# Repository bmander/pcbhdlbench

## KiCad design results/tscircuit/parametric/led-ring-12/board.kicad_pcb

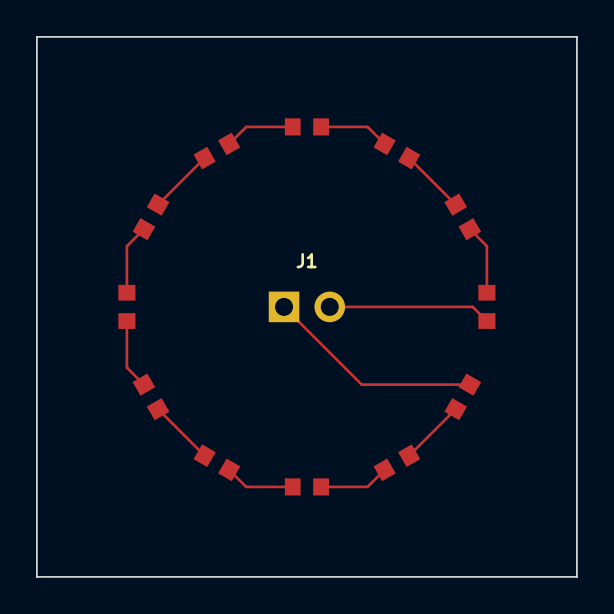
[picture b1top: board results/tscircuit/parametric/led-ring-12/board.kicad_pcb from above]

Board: 2 copper layers, 30.0 x 30.0 mm, 13 parts (0 on the bottom side), 13 nets.

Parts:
D1, D2, D3, D4, D5, D6, D7, D8, D9, D10, D11, D12: LED; led
J1: J1; pin_header_pinrow2_p2_54_id1_od1_7_nopinlabels

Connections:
.D1 > .anode to .D2 > .cathode: D1.1, D2.2
.D2 > .anode to .D3 > .cathode: D2.1, D3.2
.D3 > .anode to .D4 > .cathode: D3.1, D4.2
.D4 > .anode to .D5 > .cathode: D4.1, D5.2
.D5 > .anode to .D6 > .cathode: D5.1, D6.2
.D6 > .anode to .D7 > .cathode: D6.1, D7.2
.D7 > .anode to .D8 > .cathode: D7.1, D8.2
.D8 > .anode to .D9 > .cathode: D8.1, D9.2
.D9 > .anode to .D10 > .cathode: D9.1, D10.2
.D10 > .anode to .D11 > .cathode: D10.1, D11.2
.D11 > .anode to .D12 > .cathode: D11.1, D12.2
.J1 > .pin1 to .D12 > .anode: D12.1, J1.1
.J1 > .pin2 to .D1 > .cathode: D1.2, J1.2

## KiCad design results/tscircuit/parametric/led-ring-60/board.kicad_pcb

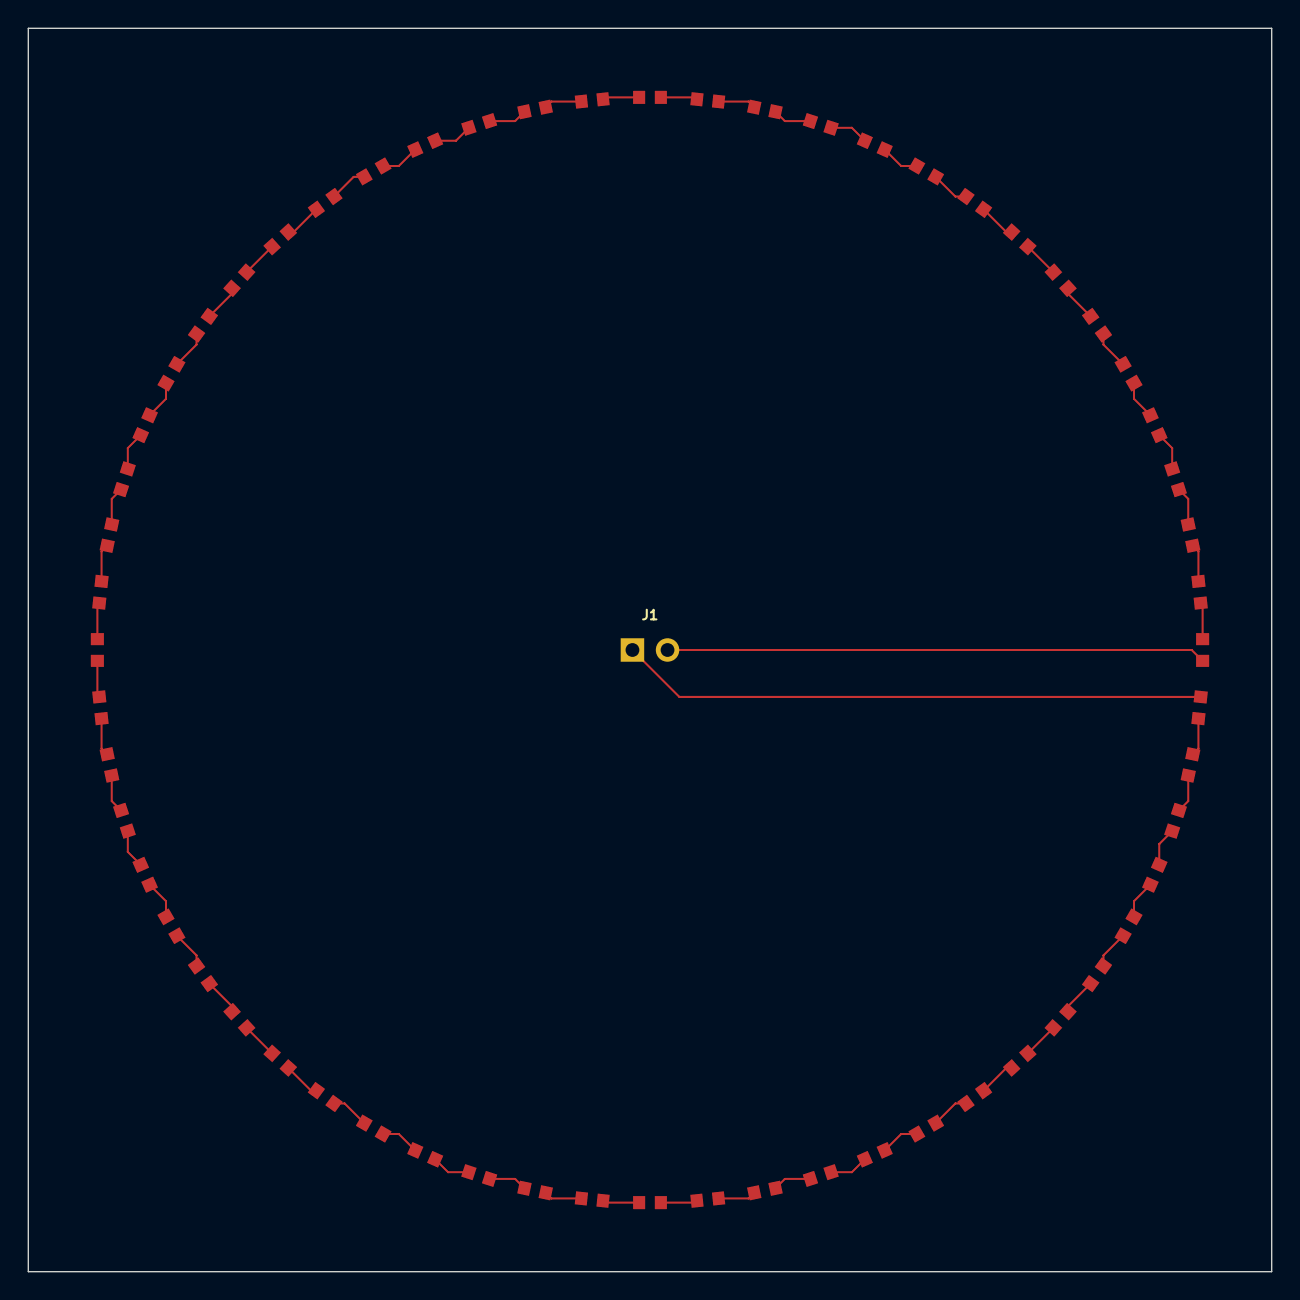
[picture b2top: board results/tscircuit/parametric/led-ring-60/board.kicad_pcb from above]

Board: 2 copper layers, 90.0 x 90.0 mm, 61 parts (0 on the bottom side), 61 nets.

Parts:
D1, D2, D3, D4, D5, D6, D7, D8, D9, D10, D11, D12, D13, D14, D15, D16, D17, D18, D19, D20, D21, D22, D23, D24, D25, D26, D27, D28, D29, D30, D31, D32, D33, D34, D35, D36, D37, D38, D39, D40, D41, D42, D43, D44, D45, D46, D47, D48, D49, D50, D51, D52, D53, D54, D55, D56, D57, D58, D59, D60: LED; led
J1: J1; pin_header_pinrow2_p2_54_id1_od1_7_nopinlabels

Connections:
.D1 > .anode to .D2 > .cathode: D1.1, D2.2
.D2 > .anode to .D3 > .cathode: D2.1, D3.2
.D3 > .anode to .D4 > .cathode: D3.1, D4.2
.D4 > .anode to .D5 > .cathode: D4.1, D5.2
.D5 > .anode to .D6 > .cathode: D5.1, D6.2
.D6 > .anode to .D7 > .cathode: D6.1, D7.2
.D7 > .anode to .D8 > .cathode: D7.1, D8.2
.D8 > .anode to .D9 > .cathode: D8.1, D9.2
.D9 > .anode to .D10 > .cathode: D9.1, D10.2
.D10 > .anode to .D11 > .cathode: D10.1, D11.2
.D11 > .anode to .D12 > .cathode: D11.1, D12.2
.D12 > .anode to .D13 > .cathode: D12.1, D13.2
.D13 > .anode to .D14 > .cathode: D13.1, D14.2
.D14 > .anode to .D15 > .cathode: D14.1, D15.2
.D15 > .anode to .D16 > .cathode: D15.1, D16.2
.D16 > .anode to .D17 > .cathode: D16.1, D17.2
.D17 > .anode to .D18 > .cathode: D17.1, D18.2
.D18 > .anode to .D19 > .cathode: D18.1, D19.2
.D19 > .anode to .D20 > .cathode: D19.1, D20.2
.D20 > .anode to .D21 > .cathode: D20.1, D21.2
.D21 > .anode to .D22 > .cathode: D21.1, D22.2
.D22 > .anode to .D23 > .cathode: D22.1, D23.2
.D23 > .anode to .D24 > .cathode: D23.1, D24.2
.D24 > .anode to .D25 > .cathode: D24.1, D25.2
.D25 > .anode to .D26 > .cathode: D25.1, D26.2
.D26 > .anode to .D27 > .cathode: D26.1, D27.2
.D27 > .anode to .D28 > .cathode: D27.1, D28.2
.D28 > .anode to .D29 > .cathode: D28.1, D29.2
.D29 > .anode to .D30 > .cathode: D29.1, D30.2
.D30 > .anode to .D31 > .cathode: D30.1, D31.2
.D31 > .anode to .D32 > .cathode: D31.1, D32.2
.D32 > .anode to .D33 > .cathode: D32.1, D33.2
.D33 > .anode to .D34 > .cathode: D33.1, D34.2
.D34 > .anode to .D35 > .cathode: D34.1, D35.2
.D35 > .anode to .D36 > .cathode: D35.1, D36.2
.D36 > .anode to .D37 > .cathode: D36.1, D37.2
.D37 > .anode to .D38 > .cathode: D37.1, D38.2
.D38 > .anode to .D39 > .cathode: D38.1, D39.2
.D39 > .anode to .D40 > .cathode: D39.1, D40.2
.D40 > .anode to .D41 > .cathode: D40.1, D41.2
.D41 > .anode to .D42 > .cathode: D41.1, D42.2
.D42 > .anode to .D43 > .cathode: D42.1, D43.2
.D43 > .anode to .D44 > .cathode: D43.1, D44.2
.D44 > .anode to .D45 > .cathode: D44.1, D45.2
.D45 > .anode to .D46 > .cathode: D45.1, D46.2
.D46 > .anode to .D47 > .cathode: D46.1, D47.2
.D47 > .anode to .D48 > .cathode: D47.1, D48.2
.D48 > .anode to .D49 > .cathode: D48.1, D49.2
.D49 > .anode to .D50 > .cathode: D49.1, D50.2
.D50 > .anode to .D51 > .cathode: D50.1, D51.2
.D51 > .anode to .D52 > .cathode: D51.1, D52.2
.D52 > .anode to .D53 > .cathode: D52.1, D53.2
.D53 > .anode to .D54 > .cathode: D53.1, D54.2
.D54 > .anode to .D55 > .cathode: D54.1, D55.2
.D55 > .anode to .D56 > .cathode: D55.1, D56.2
.D56 > .anode to .D57 > .cathode: D56.1, D57.2
.D57 > .anode to .D58 > .cathode: D57.1, D58.2
.D58 > .anode to .D59 > .cathode: D58.1, D59.2
.D59 > .anode to .D60 > .cathode: D59.1, D60.2
.J1 > .pin1 to .D60 > .anode: D60.1, J1.1
.J1 > .pin2 to .D1 > .cathode: D1.2, J1.2

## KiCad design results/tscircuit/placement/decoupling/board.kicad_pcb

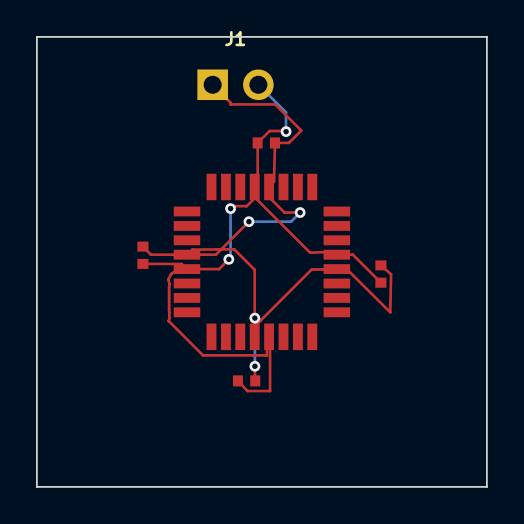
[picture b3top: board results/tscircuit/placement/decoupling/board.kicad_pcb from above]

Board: 2 copper layers, 25.0 x 25.0 mm, 6 parts (0 on the bottom side), 2 nets.

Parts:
C1, C2, C3, C4: 100nF; capacitor
J1: J1; pin_header_pinrow2_p2_54_id1_od1_7_nopinlabels
U1: chip

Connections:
GND: C1.2, C2.2, C3.2, C4.2, J1.2, U1.5, U1.13, U1.21, U1.29
VDD: C1.1, C2.1, C3.1, C4.1, J1.1, U1.4, U1.12, U1.20, U1.28

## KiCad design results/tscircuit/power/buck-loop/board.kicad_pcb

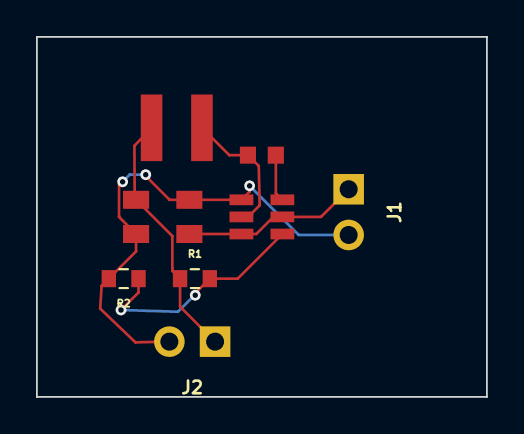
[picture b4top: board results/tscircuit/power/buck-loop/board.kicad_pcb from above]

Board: 2 copper layers, 25.0 x 20.0 mm, 9 parts (0 on the bottom side), 6 nets.

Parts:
C1: 10uF; capacitor
C2: 100nF; capacitor
C3: 22uF; capacitor
J1: J1; pin_header_pinrow2_p2_54_id1_od1_7_nopinlabels
J2: J2; pin_header_pinrow2_p2_54_id1_od1_7_nopinlabels
L1: 2.2µH; inductor
R1: 33kΩ; resistor_res0603
R2: 10kΩ; resistor_res0603
U1: chip

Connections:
BST: C2.1, U1.6
FB: R1.2, R2.1, U1.4
GND: C1.2, C3.2, J1.2, J2.2, R2.2, U1.1
SW: C2.2, L1.1, U1.2
VIN: C1.1, J1.1, U1.3, U1.5
VOUT: C3.1, J2.1, L1.2, R1.1

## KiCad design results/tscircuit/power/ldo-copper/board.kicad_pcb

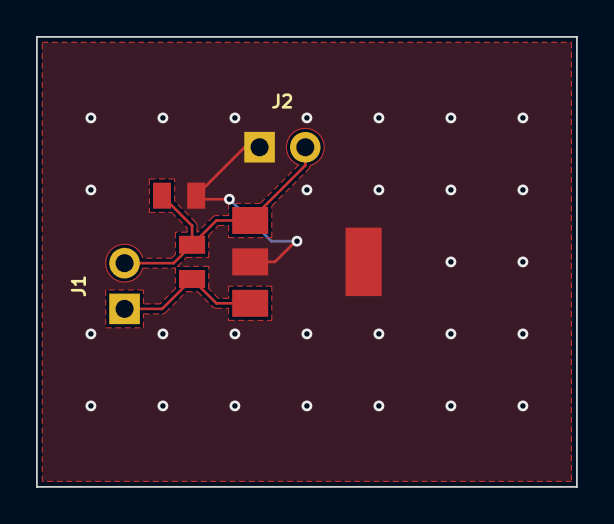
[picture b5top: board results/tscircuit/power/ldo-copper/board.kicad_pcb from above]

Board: 2 copper layers, 30.0 x 25.0 mm, 5 parts (0 on the bottom side), 3 nets.

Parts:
C1: 10uF; capacitor
C2: 22uF; capacitor
J1: J1; pin_header_pinrow2_p2_54_id1_od1_7_nopinlabels
J2: J2; pin_header_pinrow2_p2_54_id1_od1_7_nopinlabels
U1: chip

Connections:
GND: C1.2, C2.2, J1.2, J2.2, U1.1
VIN: C1.1, J1.1, U1.3
VOUT: C2.1, J2.1, U1.2

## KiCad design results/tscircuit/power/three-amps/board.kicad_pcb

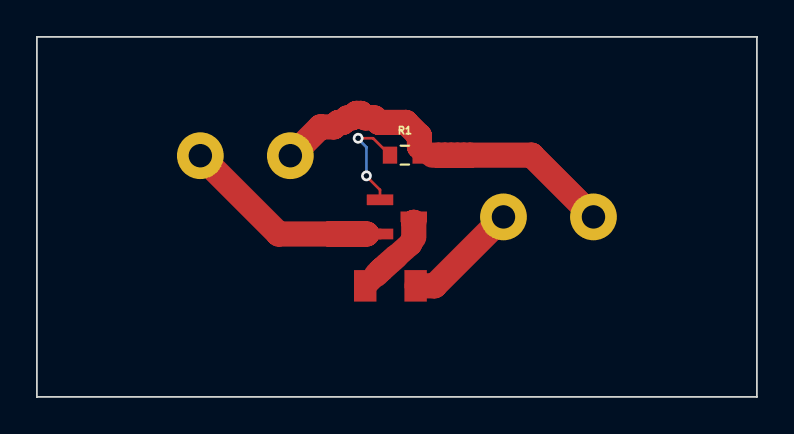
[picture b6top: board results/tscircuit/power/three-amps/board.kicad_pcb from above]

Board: 2 copper layers, 40.0 x 20.0 mm, 5 parts (0 on the bottom side), 5 nets.

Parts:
F1: chip
J1, J2: chip
Q1: chip
R1: 100kΩ; resistor_res0603

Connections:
.F1 > .pin2 to .Q1 > .D: F1.2, Q1.3
.J1 > .pin1 to .F1 > .pin1: F1.1, J1.1
.J2 > .pin2 to .J1 > .pin2: J1.2, J2.2, R1.2
.Q1 > .G to .R1 > .pin1: Q1.1, R1.1
.Q1 > .S to .J2 > .pin1: J2.1, Q1.2

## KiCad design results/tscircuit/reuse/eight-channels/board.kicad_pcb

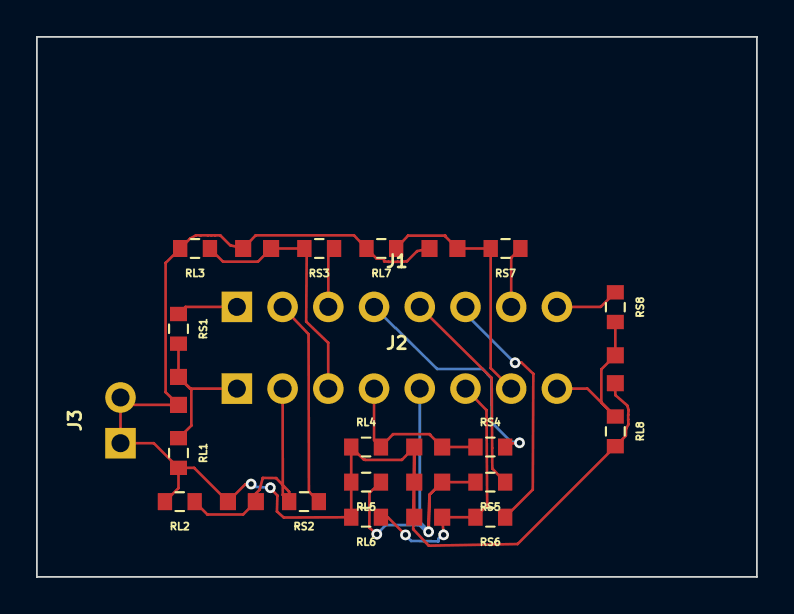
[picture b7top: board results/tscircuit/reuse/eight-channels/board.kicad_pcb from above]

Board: 2 copper layers, 40.0 x 30.0 mm, 27 parts (0 on the bottom side), 17 nets.

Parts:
C1, C2, C3, C4, C5, C6, C7, C8: 100nF; capacitor
J1: J1; pin_header_pinrow8_p2_54_id1_od1_7_nopinlabels
J2: J2; pin_header_pinrow8_p2_54_id1_od1_7_nopinlabels
J3: J3; pin_header_pinrow2_p2_54_id1_od1_7_nopinlabels
RL1, RL2, RL3, RL4, RL5, RL6, RL7, RL8: 100kΩ; resistor_res0603
RS1, RS2, RS3, RS4, RS5, RS6, RS7, RS8: 1kΩ; resistor_res0603

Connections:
GND: C1.2, C2.2, C3.2, C4.2, C5.2, C6.2, C7.2, C8.2, J3.1, J3.2, RL1.2, RL2.2, RL3.2, RL4.2, RL5.2, RL6.2, RL7.2, RL8.2
IN1: J1.1, RS1.1
IN2: J1.2, RS2.1
IN3: J1.3, RS3.1
IN4: J1.4, RS4.1
IN5: J1.5, RS5.1
IN6: J1.6, RS6.1
IN7: J1.7, RS7.1
IN8: J1.8, RS8.1
OUT1: C1.1, J2.1, RL1.1, RS1.2
OUT2: C2.1, J2.2, RL2.1, RS2.2
OUT3: C3.1, J2.3, RL3.1, RS3.2
OUT4: C4.1, J2.4, RL4.1, RS4.2
OUT5: C5.1, J2.5, RL5.1, RS5.2
OUT6: C6.1, J2.6, RL6.1, RS6.2
OUT7: C7.1, J2.7, RL7.1, RS7.2
OUT8: C8.1, J2.8, RL8.1, RS8.2

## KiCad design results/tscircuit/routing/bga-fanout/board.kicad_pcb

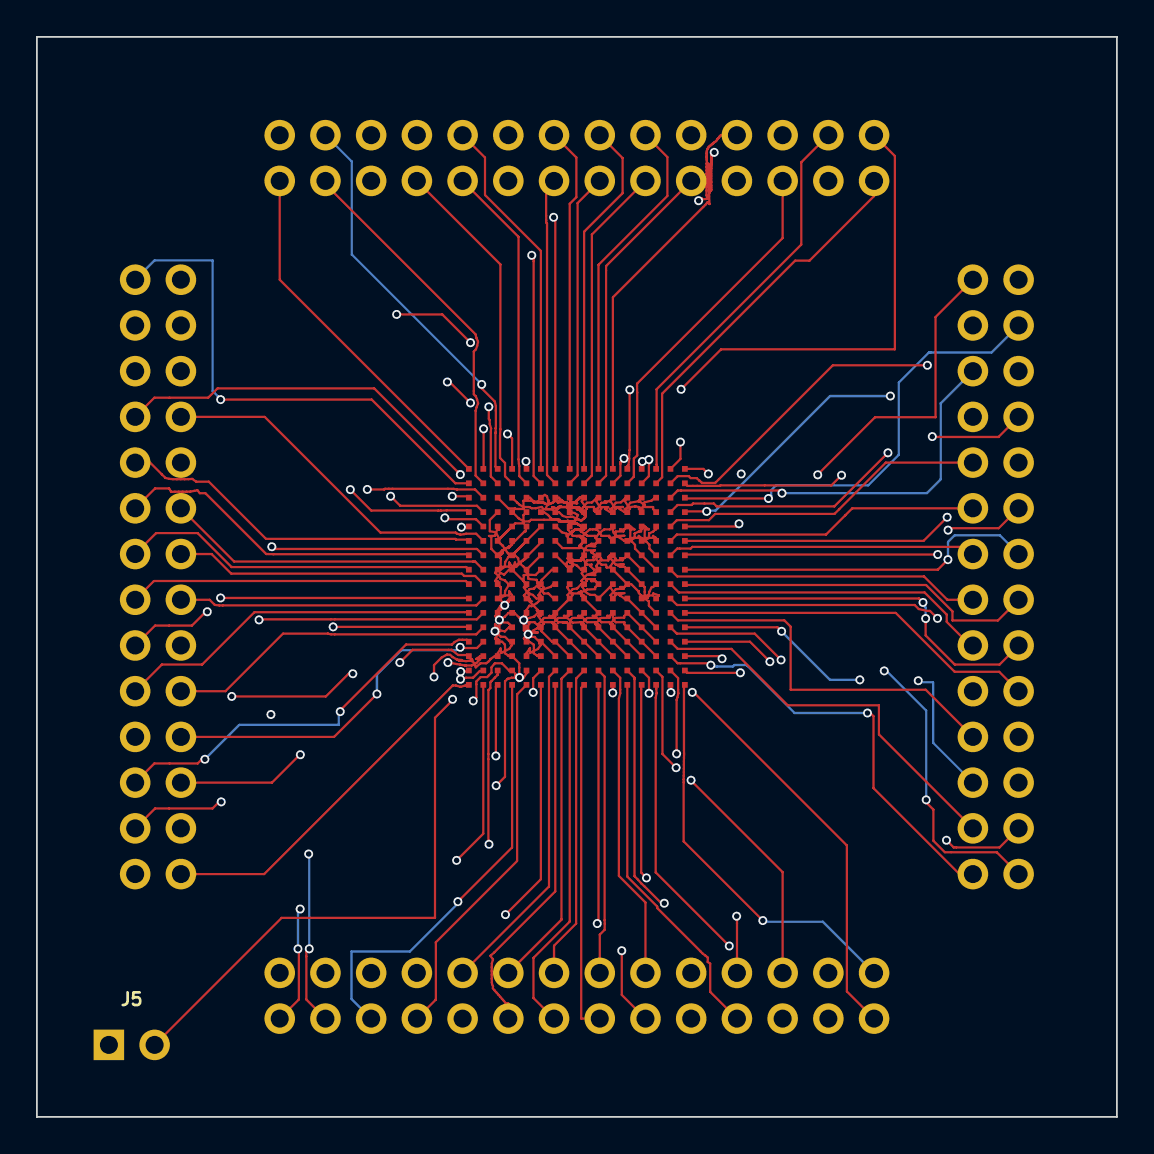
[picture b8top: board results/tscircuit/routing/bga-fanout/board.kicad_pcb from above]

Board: 4 copper layers, 60.0 x 60.0 mm, 6 parts (0 on the bottom side), 114 nets.

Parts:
J1, J2, J3, J4: chip
J5: J5; pin_header_pinrow2_p2_54_id1_od1_7_nopinlabels
U1: chip

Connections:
.U1 > .A1 to .J1 > .pin1: J1.1, U1.1
.U1 > .A2 to .J1 > .pin2: J1.2, U1.2
.U1 > .A3 to .J1 > .pin4: J1.4, U1.3
.U1 > .A4 to .J1 > .pin6: J1.6, U1.4
.U1 > .A5 to .J1 > .pin8: J1.8, U1.5
.U1 > .A6 to .J1 > .pin10: J1.10, U1.6
.U1 > .A7 to .J1 > .pin12: J1.12, U1.7
.U1 > .A8 to .J1 > .pin14: J1.14, U1.8
.U1 > .A9 to .J1 > .pin16: J1.16, U1.9
.U1 > .A10 to .J1 > .pin18: J1.18, U1.10
.U1 > .A11 to .J1 > .pin20: J1.20, U1.11
.U1 > .A12 to .J1 > .pin22: J1.22, U1.12
.U1 > .A13 to .J1 > .pin24: J1.24, U1.13
.U1 > .A14 to .J1 > .pin26: J1.26, U1.14
.U1 > .A15 to .J1 > .pin28: J1.28, U1.15
.U1 > .A16 to .J2 > .pin1: J2.1, U1.16
.U1 > .B1 to .J4 > .pin28: J4.28, U1.17
.U1 > .B2 to .J1 > .pin3: J1.3, U1.18
.U1 > .B3 to .J1 > .pin5: J1.5, U1.19
.U1 > .B4 to .J1 > .pin7: J1.7, U1.20
.U1 > .B5 to .J1 > .pin9: J1.9, U1.21
.U1 > .B6 to .J1 > .pin11: J1.11, U1.22
.U1 > .B7 to .J1 > .pin13: J1.13, U1.23
.U1 > .B8 to .J1 > .pin15: J1.15, U1.24
.U1 > .B9 to .J1 > .pin17: J1.17, U1.25
.U1 > .B10 to .J1 > .pin19: J1.19, U1.26
.U1 > .B11 to .J1 > .pin21: J1.21, U1.27
.U1 > .B12 to .J1 > .pin23: J1.23, U1.28
.U1 > .B13 to .J1 > .pin25: J1.25, U1.29
.U1 > .B14 to .J1 > .pin27: J1.27, U1.30
.U1 > .B15 to .J2 > .pin3: J2.3, U1.31
.U1 > .B16 to .J2 > .pin2: J2.2, U1.32
.U1 > .C1 to .J4 > .pin26: J4.26, U1.33
.U1 > .C2 to .J4 > .pin27: J4.27, U1.34
.U1 > .C15 to .J2 > .pin5: J2.5, U1.47
.U1 > .C16 to .J2 > .pin4: J2.4, U1.48
.U1 > .D1 to .J4 > .pin24: J4.24, U1.49
.U1 > .D2 to .J4 > .pin25: J4.25, U1.50
.U1 > .D15 to .J2 > .pin7: J2.7, U1.63
.U1 > .D16 to .J2 > .pin6: J2.6, U1.64
.U1 > .E1 to .J4 > .pin22: J4.22, U1.65
.U1 > .E2 to .J4 > .pin23: J4.23, U1.66
.U1 > .E15 to .J2 > .pin9: J2.9, U1.79
.U1 > .E16 to .J2 > .pin8: J2.8, U1.80
.U1 > .F1 to .J4 > .pin20: J4.20, U1.81
.U1 > .F2 to .J4 > .pin21: J4.21, U1.82
.U1 > .F15 to .J2 > .pin11: J2.11, U1.95
.U1 > .F16 to .J2 > .pin10: J2.10, U1.96
.U1 > .G1 to .J4 > .pin18: J4.18, U1.97
.U1 > .G2 to .J4 > .pin19: J4.19, U1.98
.U1 > .G15 to .J2 > .pin13: J2.13, U1.111
.U1 > .G16 to .J2 > .pin12: J2.12, U1.112
.U1 > .H1 to .J4 > .pin16: J4.16, U1.113
.U1 > .H2 to .J4 > .pin17: J4.17, U1.114
.U1 > .H15 to .J2 > .pin15: J2.15, U1.127
.U1 > .H16 to .J2 > .pin14: J2.14, U1.128
.U1 > .J1 to .J4 > .pin14: J4.14, U1.129
.U1 > .J2 to .J4 > .pin15: J4.15, U1.130
.U1 > .J15 to .J2 > .pin17: J2.17, U1.143
.U1 > .J16 to .J2 > .pin16: J2.16, U1.144
.U1 > .K1 to .J4 > .pin12: J4.12, U1.145
.U1 > .K2 to .J4 > .pin13: J4.13, U1.146
.U1 > .K15 to .J2 > .pin19: J2.19, U1.159
.U1 > .K16 to .J2 > .pin18: J2.18, U1.160
.U1 > .L1 to .J4 > .pin10: J4.10, U1.161
.U1 > .L2 to .J4 > .pin11: J4.11, U1.162
.U1 > .L15 to .J2 > .pin21: J2.21, U1.175
.U1 > .L16 to .J2 > .pin20: J2.20, U1.176
.U1 > .M1 to .J4 > .pin8: J4.8, U1.177
.U1 > .M2 to .J4 > .pin9: J4.9, U1.178
.U1 > .M15 to .J2 > .pin23: J2.23, U1.191
.U1 > .M16 to .J2 > .pin22: J2.22, U1.192
.U1 > .N1 to .J4 > .pin6: J4.6, U1.193
.U1 > .N2 to .J4 > .pin7: J4.7, U1.194
.U1 > .N15 to .J2 > .pin25: J2.25, U1.207
.U1 > .N16 to .J2 > .pin24: J2.24, U1.208
.U1 > .P1 to .J4 > .pin4: J4.4, U1.209
.U1 > .P2 to .J4 > .pin5: J4.5, U1.210
.U1 > .P15 to .J2 > .pin27: J2.27, U1.223
.U1 > .P16 to .J2 > .pin26: J2.26, U1.224
.U1 > .R1 to .J4 > .pin2: J4.2, U1.225
.U1 > .R2 to .J4 > .pin3: J4.3, U1.226
.U1 > .R3 to .J3 > .pin27: J3.27, U1.227
.U1 > .R4 to .J3 > .pin25: J3.25, U1.228
.U1 > .R5 to .J3 > .pin23: J3.23, U1.229
.U1 > .R6 to .J3 > .pin21: J3.21, U1.230
.U1 > .R7 to .J3 > .pin19: J3.19, U1.231
.U1 > .R8 to .J3 > .pin17: J3.17, U1.232
.U1 > .R9 to .J3 > .pin15: J3.15, U1.233
.U1 > .R10 to .J3 > .pin13: J3.13, U1.234
.U1 > .R11 to .J3 > .pin11: J3.11, U1.235
.U1 > .R12 to .J3 > .pin9: J3.9, U1.236
.U1 > .R13 to .J3 > .pin7: J3.7, U1.237
.U1 > .R14 to .J3 > .pin5: J3.5, U1.238
.U1 > .R15 to .J3 > .pin3: J3.3, U1.239
.U1 > .R16 to .J2 > .pin28: J2.28, U1.240
.U1 > .T1 to .J4 > .pin1: J4.1, U1.241
.U1 > .T2 to .J3 > .pin28: J3.28, U1.242
.U1 > .T3 to .J3 > .pin26: J3.26, U1.243
.U1 > .T4 to .J3 > .pin24: J3.24, U1.244
.U1 > .T5 to .J3 > .pin22: J3.22, U1.245
.U1 > .T6 to .J3 > .pin20: J3.20, U1.246
.U1 > .T7 to .J3 > .pin18: J3.18, U1.247
.U1 > .T8 to .J3 > .pin16: J3.16, U1.248
.U1 > .T9 to .J3 > .pin14: J3.14, U1.249
.U1 > .T10 to .J3 > .pin12: J3.12, U1.250
.U1 > .T11 to .J3 > .pin10: J3.10, U1.251
.U1 > .T12 to .J3 > .pin8: J3.8, U1.252
.U1 > .T13 to .J3 > .pin6: J3.6, U1.253
.U1 > .T14 to .J3 > .pin4: J3.4, U1.254
.U1 > .T15 to .J3 > .pin2: J3.2, U1.255
.U1 > .T16 to .J3 > .pin1: J3.1, U1.256
GND: J5.2, U1.35, U1.37, U1.39, U1.41, U1.43, U1.45, U1.52, U1.54, U1.56, U1.58, U1.60, U1.62, U1.67, U1.69, U1.71, U1.73, U1.75, U1.77, U1.84, U1.86, U1.88, U1.90, U1.92, U1.94, U1.99, U1.101, U1.103, U1.105, U1.107, U1.109, U1.116, U1.118, U1.120, U1.122, U1.124, U1.126, U1.131, U1.133, U1.135, U1.137, U1.139, U1.141, U1.148, U1.150, U1.152, U1.154, U1.156, U1.158, U1.163, U1.165, U1.167, U1.169, U1.171, U1.173, U1.180, U1.182, U1.184, U1.186, U1.188, U1.190, U1.195, U1.197, U1.199, U1.201, U1.203, U1.205, U1.212, U1.214, U1.216, U1.218, U1.220, U1.222
VCC: J5.1, U1.36, U1.38, U1.40, U1.42, U1.44, U1.46, U1.51, U1.53, U1.55, U1.57, U1.59, U1.61, U1.68, U1.70, U1.72, U1.74, U1.76, U1.78, U1.83, U1.85, U1.87, U1.89, U1.91, U1.93, U1.100, U1.102, U1.104, U1.106, U1.108, U1.110, U1.115, U1.117, U1.119, U1.121, U1.123, U1.125, U1.132, U1.134, U1.136, U1.138, U1.140, U1.142, U1.147, U1.149, U1.151, U1.153, U1.155, U1.157, U1.164, U1.166, U1.168, U1.170, U1.172, U1.174, U1.179, U1.181, U1.183, U1.185, U1.187, U1.189, U1.196, U1.198, U1.200, U1.202, U1.204, U1.206, U1.211, U1.213, U1.215, U1.217, U1.219, U1.221
